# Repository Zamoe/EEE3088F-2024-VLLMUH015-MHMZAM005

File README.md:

# EEE3088F-2024-VLLMUH015-MHMZAM005 - Group 29
Git Repo for EEE3088F group 29 2024 at the University of Cape Town.

The project for EEE3088F aims to design subassemblies for a micromouse, namely the power and sensing subsystem. 
The GitHub repo contains the Kicad Project files for the final PCBs for the project.

The power system is done by Muhammed Vally - VLLMUH015
The sensing subsystem is done by Zameer Mahomed - MHMZAM005

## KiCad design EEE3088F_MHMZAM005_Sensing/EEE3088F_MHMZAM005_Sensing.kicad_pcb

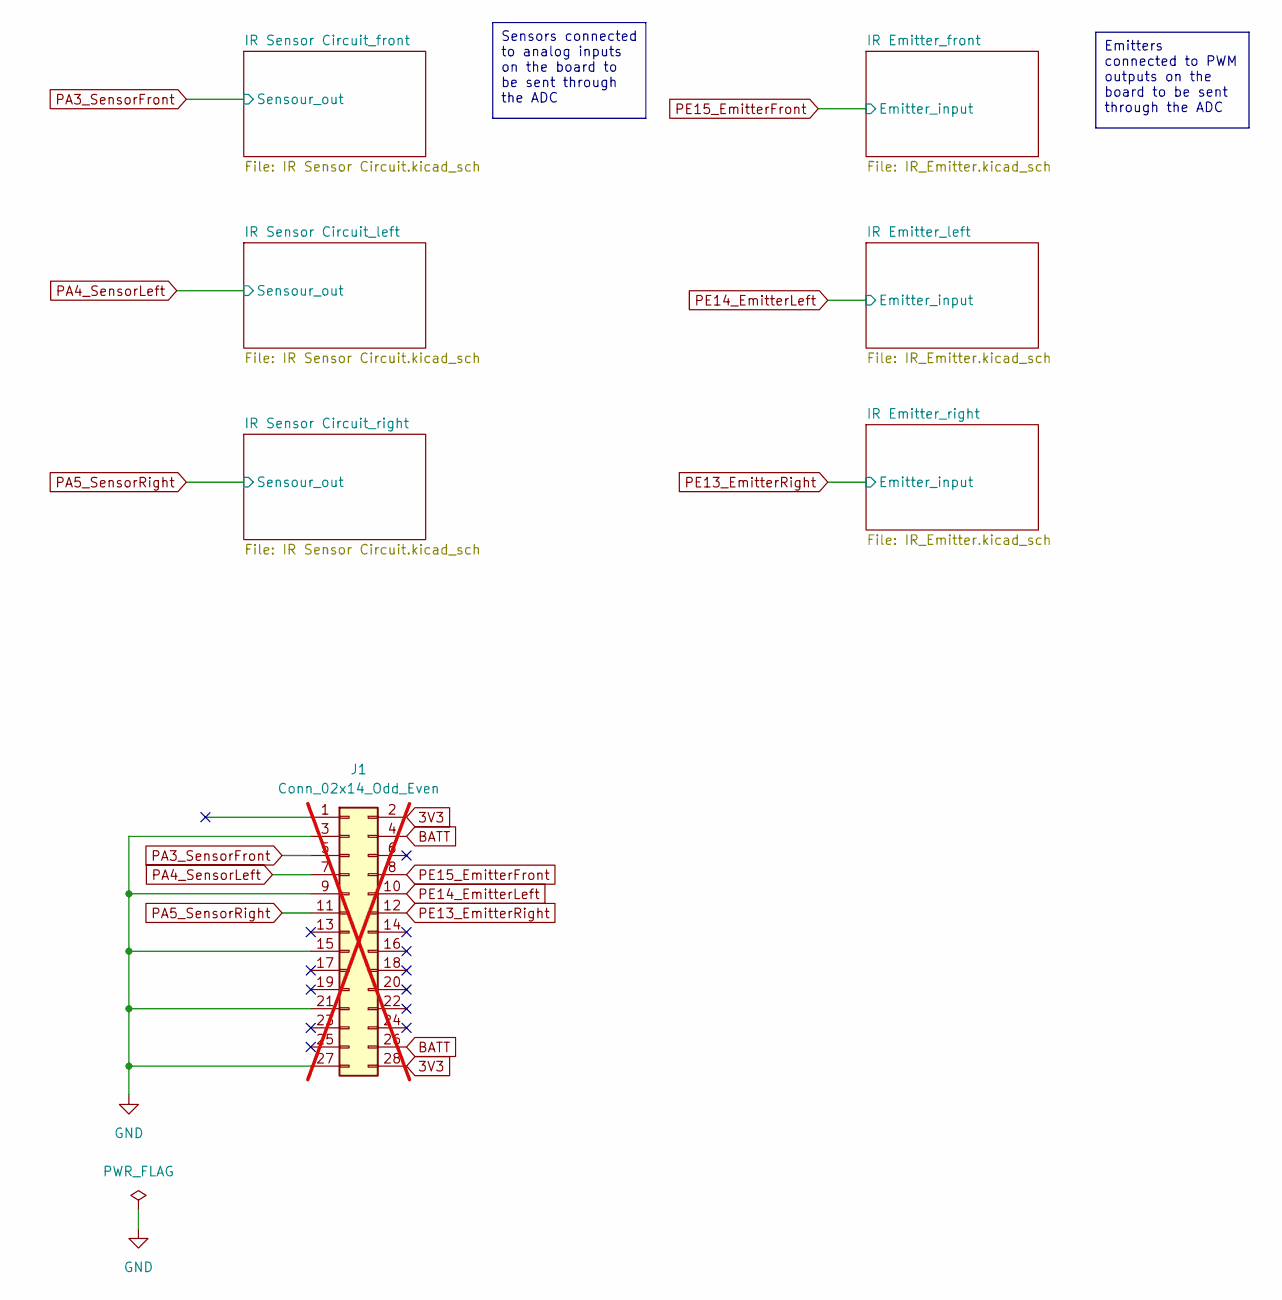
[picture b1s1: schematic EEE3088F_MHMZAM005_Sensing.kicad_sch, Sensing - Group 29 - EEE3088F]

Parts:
J1: Conn_02x14_Odd_Even; PinHeader_2x14_P2.54mm_Vertical; not fitted

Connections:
3V3: J1.2, J1.28; also elsewhere on the board
BATT: J1.4, J1.26
GND: J1.3, J1.9, J1.15, J1.21, J1.27; also elsewhere on the board
PA3: J1.5; also elsewhere on the board
PA4: J1.7; also elsewhere on the board
PA5: J1.11; also elsewhere on the board
PE13: J1.12; also elsewhere on the board
PE14: J1.10; also elsewhere on the board
PE15: J1.8; also elsewhere on the board

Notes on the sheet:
Sensors connected to analog inputs on the board to be sent through the ADC
Emitters connected to PWM outputs on the board to be sent through the ADC

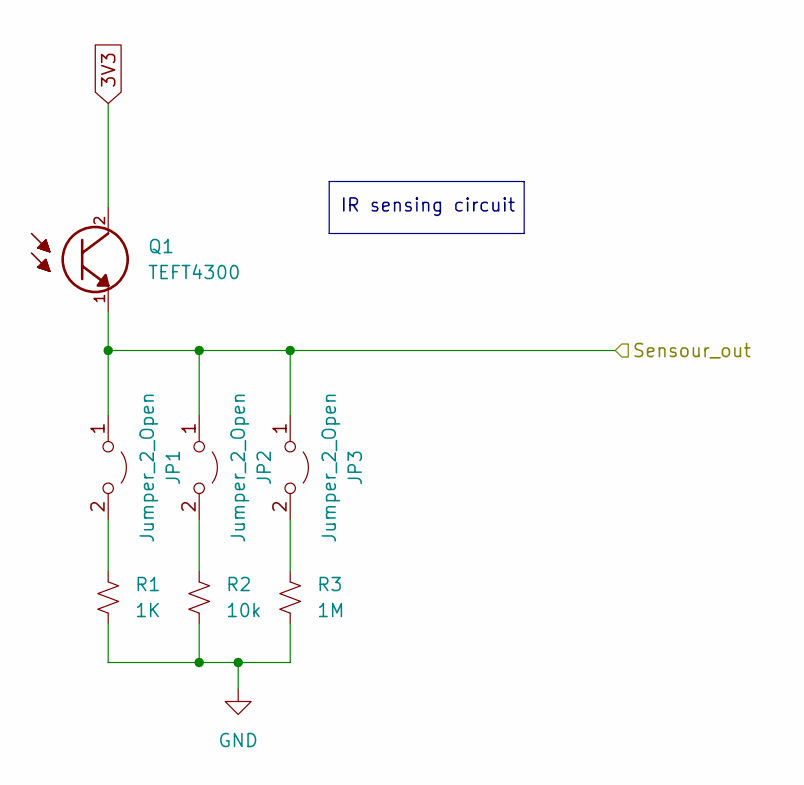
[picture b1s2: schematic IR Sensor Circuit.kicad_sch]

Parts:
JP1, JP2, JP3: Jumper_2_Open; SolderJumper-2_P1.3mm_Open_Pad1.0x1.5mm
Q1: TEFT4300; LED_D3.0mm_Horizontal_O1.27mm_Z2.0mm; LCSC C118301
R1: 1K; R_Axial_DIN0207_L6.3mm_D2.5mm_P2.54mm_Vertical; LCSC C274526
R2: 10k; R_Axial_DIN0207_L6.3mm_D2.5mm_P2.54mm_Vertical; LCSC C274420
R3: 1M; R_Axial_DIN0207_L6.3mm_D2.5mm_P2.54mm_Vertical; LCSC C2894664

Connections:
3V3: Q1.2; also elsewhere on the board
GND: R1.2, R2.2, R3.1; also elsewhere on the board
unnamed: JP1.2 (B), R1.1
unnamed: JP2.2 (B), R2.1
unnamed: JP3.2 (B), R3.2
PA3: JP1.1 (A), JP2.1 (A), JP3.1 (A), Q1.1; also elsewhere on the board

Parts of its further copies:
JP4, JP5, JP6, JP7, JP8, JP9: Jumper_2_Open; SolderJumper-2_P1.3mm_Open_Pad1.0x1.5mm
Q2, Q3: TEFT4300; LED_D3.0mm_Horizontal_O1.27mm_Z2.0mm; LCSC C118301
R4, R7: 1K; R_Axial_DIN0207_L6.3mm_D2.5mm_P2.54mm_Vertical; LCSC C274526
R5, R8: 10k; R_Axial_DIN0207_L6.3mm_D2.5mm_P2.54mm_Vertical; LCSC C274420
R6, R9: 1M; R_Axial_DIN0207_L6.3mm_D2.5mm_P2.54mm_Vertical; LCSC C2894664

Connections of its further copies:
3V3: Q2.2, Q3.2; also elsewhere on the board
GND: R4.2, R5.2, R6.1, R7.2, R8.2, R9.1; also elsewhere on the board
unnamed: JP4.2 (B), R4.1
unnamed: JP5.2 (B), R5.1
unnamed: JP6.2 (B), R6.2
unnamed: JP7.2 (B), R7.1
unnamed: JP8.2 (B), R8.1
unnamed: JP9.2 (B), R9.2
PA4: JP4.1 (A), JP5.1 (A), JP6.1 (A), Q2.1; also elsewhere on the board
PA5: JP7.1 (A), JP8.1 (A), JP9.1 (A), Q3.1; also elsewhere on the board

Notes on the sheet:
IR sensing circuit

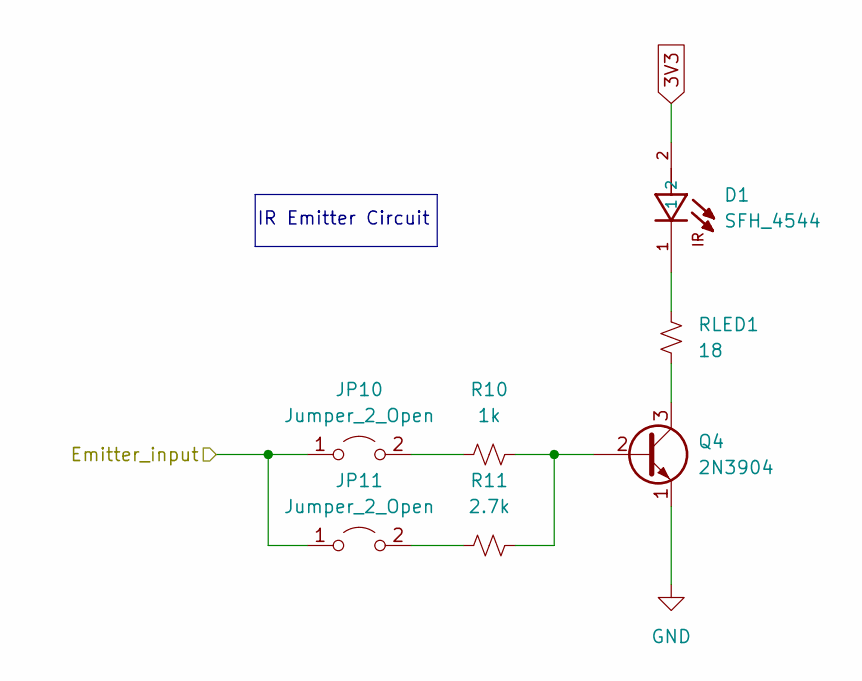
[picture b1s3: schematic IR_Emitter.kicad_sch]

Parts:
D1: SFH_4544; LED_D5.0mm_Horizontal_O1.27mm_Z9.0mm; PARTREV 1.3; LCSC C2900370
JP10, JP11: Jumper_2_Open; SolderJumper-2_P1.3mm_Open_Pad1.0x1.5mm
Q4: 2N3904; TO-92_Inline; LCSC C118538
R10: 1k; R_Axial_DIN0207_L6.3mm_D2.5mm_P2.54mm_Vertical; LCSC C274526
R11: 2.7k; R_Axial_DIN0207_L6.3mm_D2.5mm_P2.54mm_Vertical; LCSC C119880
RLED1: 18; R_Axial_DIN0207_L6.3mm_D2.5mm_P2.54mm_Vertical; LCSC C172523

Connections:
3V3: D1.2; also elsewhere on the board
GND: Q4.1 (E); also elsewhere on the board
unnamed: D1.1, RLED1.2
unnamed: JP10.2 (B), R10.2
unnamed: JP11.2 (B), R11.1
unnamed: Q4.2 (B), R10.1, R11.2
unnamed: Q4.3 (C), RLED1.1
PE15: JP10.1 (A), JP11.1 (A); also elsewhere on the board

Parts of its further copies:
D2, D3: SFH_4544; LED_D5.0mm_Horizontal_O1.27mm_Z9.0mm; PARTREV 1.3; LCSC C2900370
JP12, JP13, JP14, JP15: Jumper_2_Open; SolderJumper-2_P1.3mm_Open_Pad1.0x1.5mm
Q5, Q6: 2N3904; TO-92_Inline; LCSC C118538
R12, R14: 1k; R_Axial_DIN0207_L6.3mm_D2.5mm_P2.54mm_Vertical; LCSC C274526
R13, R15: 2.7k; R_Axial_DIN0207_L6.3mm_D2.5mm_P2.54mm_Vertical; LCSC C119880
RLED2, RLED3: 18; R_Axial_DIN0207_L6.3mm_D2.5mm_P2.54mm_Vertical; LCSC C172523

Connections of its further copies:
3V3: D2.2, D3.2; also elsewhere on the board
GND: Q5.1 (E), Q6.1 (E); also elsewhere on the board
unnamed: D2.1, RLED2.2
unnamed: D3.1, RLED3.2
unnamed: JP12.2 (B), R12.2
unnamed: JP13.2 (B), R13.1
unnamed: JP14.2 (B), R14.2
unnamed: JP15.2 (B), R15.1
unnamed: Q5.2 (B), R12.1, R13.2
unnamed: Q5.3 (C), RLED2.1
unnamed: Q6.2 (B), R14.1, R15.2
unnamed: Q6.3 (C), RLED3.1
PE13: JP14.1 (A), JP15.1 (A); also elsewhere on the board
PE14: JP12.1 (A), JP13.1 (A); also elsewhere on the board

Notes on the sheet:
IR Emitter Circuit

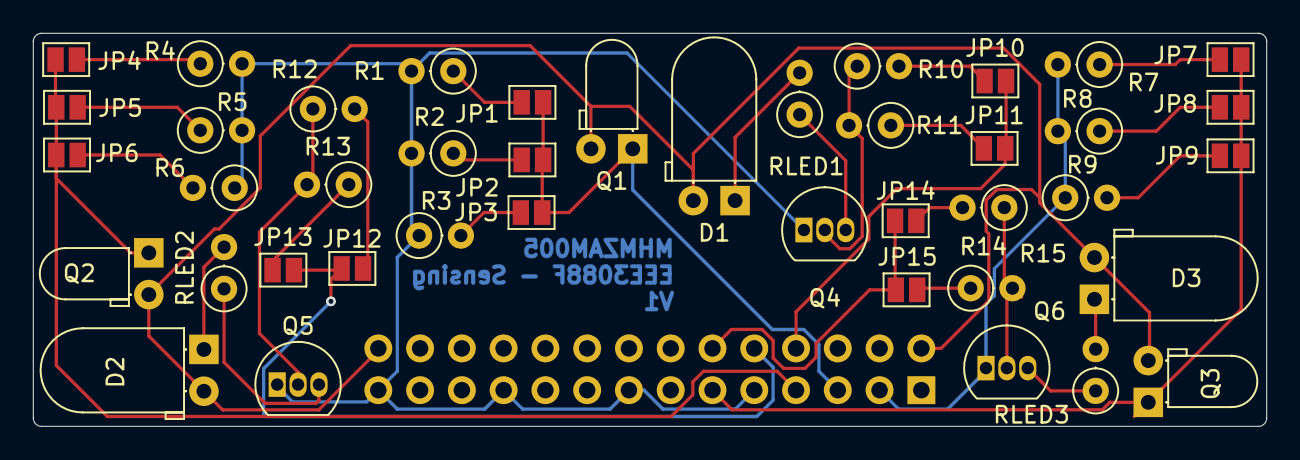
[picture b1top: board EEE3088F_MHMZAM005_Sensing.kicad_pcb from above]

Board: 2 copper layers, 75.0 x 23.9 mm, 43 parts (1 on the bottom side), 33 nets.

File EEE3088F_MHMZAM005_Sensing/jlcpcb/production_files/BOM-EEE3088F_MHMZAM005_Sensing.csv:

Comment,Designator,Footprint,LCSC
TEFT4300,"Q1,Q2,Q3",LED_D3.0mm_Horizontal_O1.27mm_Z2.0mm,C118301
2N3904,"Q4,Q5,Q6",TO-92_Inline,C118538
2.7k,"R11,R13,R15",R_Axial_DIN0207_L6.3mm_D2.5mm_P2.54mm_Vertical,C119880
18,"RLED1,RLED2,RLED3",R_Axial_DIN0207_L6.3mm_D2.5mm_P2.54mm_Vertical,C172523
10k,"R2,R5,R8",R_Axial_DIN0207_L6.3mm_D2.5mm_P2.54mm_Vertical,C274420
1K,"R1,R10,R12,R14,R4,R7",R_Axial_DIN0207_L6.3mm_D2.5mm_P2.54mm_Vertical,C274526
1M,"R3,R6,R9",R_Axial_DIN0207_L6.3mm_D2.5mm_P2.54mm_Vertical,C2894664
SFH_4544,"D1,D2,D3",LED_D5.0mm_Horizontal_O1.27mm_Z9.0mm,C2900370
Jumper_2_Open,JP4,SolderJumper-2_P1.3mm_Open_Pad1.0x1.5mm,
Jumper_2_Open,JP1,SolderJumper-2_P1.3mm_Open_Pad1.0x1.5mm,
Jumper_2_Open,JP15,SolderJumper-2_P1.3mm_Open_Pad1.0x1.5mm,
Jumper_2_Open,JP13,SolderJumper-2_P1.3mm_Open_Pad1.0x1.5mm,
Jumper_2_Open,JP2,SolderJumper-2_P1.3mm_Open_Pad1.0x1.5mm,
Jumper_2_Open,JP7,SolderJumper-2_P1.3mm_Open_Pad1.0x1.5mm,
Jumper_2_Open,JP5,SolderJumper-2_P1.3mm_Open_Pad1.0x1.5mm,
Jumper_2_Open,JP11,SolderJumper-2_P1.3mm_Open_Pad1.0x1.5mm,
Jumper_2_Open,JP9,SolderJumper-2_P1.3mm_Open_Pad1.0x1.5mm,
Jumper_2_Open,JP6,SolderJumper-2_P1.3mm_Open_Pad1.0x1.5mm,
Jumper_2_Open,JP10,SolderJumper-2_P1.3mm_Open_Pad1.0x1.5mm,
Jumper_2_Open,JP14,SolderJumper-2_P1.3mm_Open_Pad1.0x1.5mm,
Jumper_2_Open,JP3,SolderJumper-2_P1.3mm_Open_Pad1.0x1.5mm,
Jumper_2_Open,JP12,SolderJumper-2_P1.3mm_Open_Pad1.0x1.5mm,
Jumper_2_Open,JP8,SolderJumper-2_P1.3mm_Open_Pad1.0x1.5mm,
Conn_02x14_Odd_Even,J1,PinHeader_2x14_P2.54mm_Vertical,

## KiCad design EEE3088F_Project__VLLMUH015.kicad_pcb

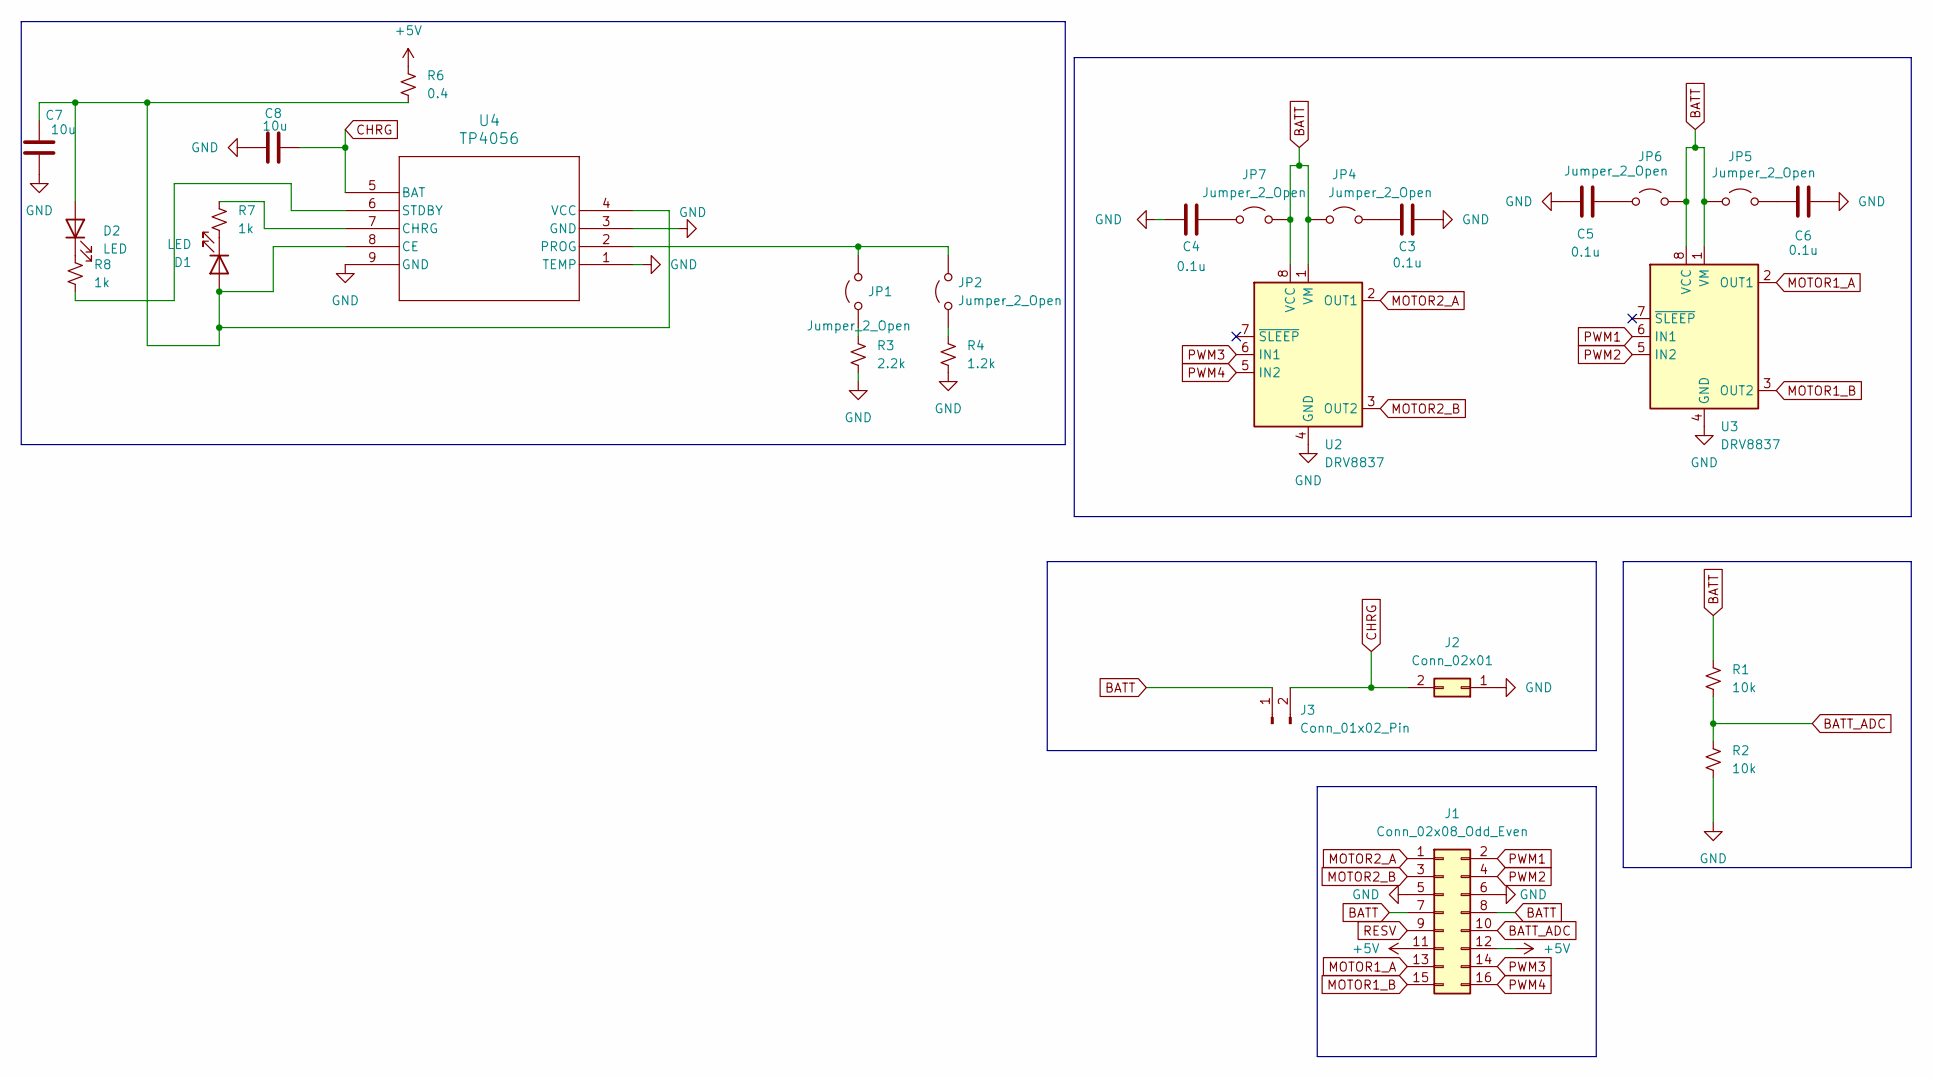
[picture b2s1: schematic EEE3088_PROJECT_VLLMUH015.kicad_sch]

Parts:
C3, C4, C5, C6: 0.1u; C_0805_2012Metric
C7, C8: 10u; C_0805_2012Metric
D1, D2: LED; LED_D1.8mm_W1.8mm_H2.4mm_Horizontal_O1.27mm_Z1.6mm
J1: Conn_02x08_Odd_Even; PinSocket_2x08_P2.54mm_Horizontal
J2: Conn_02x01; PinSocket_1x02_P2.54mm_Vertical
J3: Conn_01x02_Pin; PinHeader_1x02_P2.54mm_Vertical
JP1, JP2, JP4, JP5, JP6, JP7: Jumper_2_Open; SolderJumper-2_P1.3mm_Bridged2Bar_Pad1.0x1.5mm
R1, R2: 10k; R_0805_2012Metric
R3: 2.2k; R_0805_2012Metric
R4: 1.2k; R_0805_2012Metric
R6: 0.4; R_0805_2012Metric
R7, R8: 1k; R_0805_2012Metric
U2, U3: DRV8837; WSON-8-1EP_2x2mm_P0.5mm_EP0.9x1.6mm
U4: TP4056; ESOP8_UMW-L

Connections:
+5V: J1.11, J1.12, R6.1
BATT: J1.7, J1.8, J3.1, JP4.1 (A), JP5.1 (A), JP6.2 (B), JP7.2 (B), R1.1, U2.1 (VM), U2.8 (VCC), U3.1 (VM), U3.8 (VCC)
BATT_ADC: J1.10, R1.2, R2.1
CHRG: C8.2, J2.2, J3.2, U4.5 (BAT)
GND: C3.2, C4.1, C5.1, C6.2, C7.2, C8.1, J1.5, J1.6, J2.1, R2.2, R3.2, R4.2, U2.4 (GND), U2.9 (GND), U3.4 (GND), U3.9 (GND), U4.1 (TEMP), U4.3 (GND), U4.9 (GND)
MOTOR1_A: J1.13, U3.2 (OUT1)
MOTOR1_B: J1.15, U3.3 (OUT2)
MOTOR2_A: J1.1, U2.2 (OUT1)
MOTOR2_B: J1.3, U2.3 (OUT2)
unnamed: C7.1, D1.2 (A), D2.2 (A), R6.2, U4.4 (VCC), U4.8 (CE)
unnamed: D1.1 (K), R7.2
unnamed: D2.1 (K), R8.2
unnamed: JP1.1 (A), R3.1
unnamed: JP1.2 (B), JP2.2 (B), U4.2 (PROG)
unnamed: JP2.1 (A), R4.1
unnamed: C3.1, JP4.2 (B)
unnamed: C6.1, JP5.2 (B)
unnamed: C5.2, JP6.1 (A)
unnamed: C4.2, JP7.1 (A)
unnamed: R7.1, U4.7 (CHRG)
unnamed: R8.1, U4.6 (STDBY)
PWM1: J1.2, U3.6 (IN1)
PWM2: J1.4, U3.5 (IN2)
PWM3: J1.14, U2.6 (IN1)
PWM4: J1.16, U2.5 (IN2)
RESV: J1.9

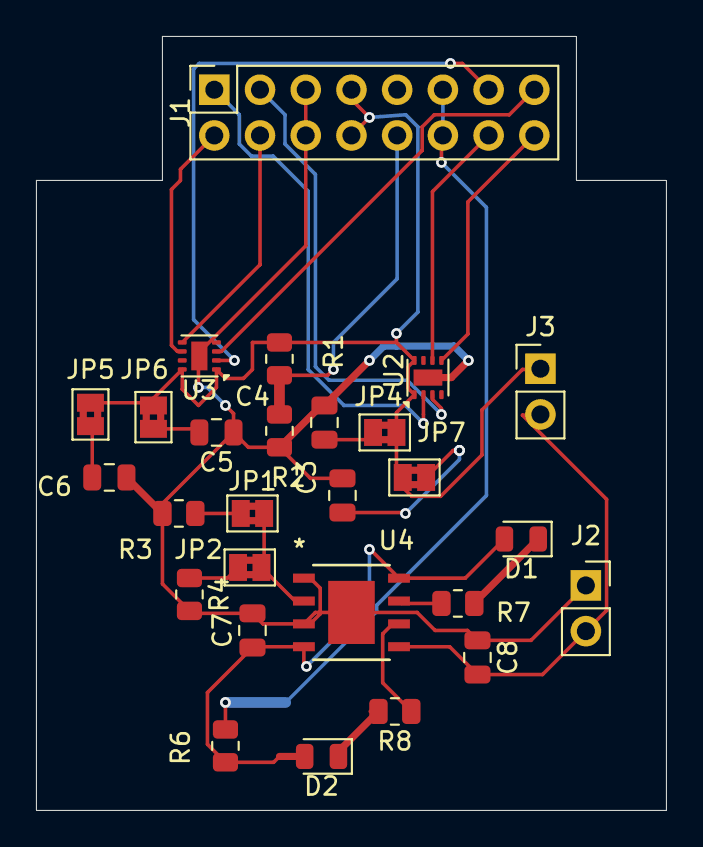
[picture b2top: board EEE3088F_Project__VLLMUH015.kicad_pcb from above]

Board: 2 copper layers, 35.0 x 43.0 mm, 27 parts (0 on the bottom side), 25 nets.

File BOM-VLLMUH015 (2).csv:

Comment,Designator,Footprint,LCSC
0.1u,C6,C_0805_2012Metric,
10k,R2,R_0805_2012Metric,
0.1u,C5,C_0805_2012Metric,
0.1u,C3,C_0805_2012Metric,
Jumper_2_Open,JP5,SolderJumper-2_P1.3mm_Bridged2Bar_Pad1.0x1.5mm,
1.1k,R4,R_0805_2012Metric,
Jumper_2_Open,JP4,SolderJumper-2_P1.3mm_Bridged2Bar_Pad1.0x1.5mm,
2.2k,R3,R_0805_2012Metric,
10k,R1,R_0805_2012Metric,
Conn_02x01,J2,PinSocket_1x02_P2.54mm_Vertical,
Jumper_2_Open,JP7,SolderJumper-2_P1.3mm_Bridged2Bar_Pad1.0x1.5mm,
Jumper_2_Open,JP2,SolderJumper-2_P1.3mm_Bridged2Bar_Pad1.0x1.5mm,
Jumper_2_Open,JP1,SolderJumper-2_P1.3mm_Bridged2Bar_Pad1.0x1.5mm,
0.1u,C4,C_0805_2012Metric,
Conn_02x08_Odd_Even,J1,PinSocket_2x08_P2.54mm_Vertical,
DRV8837,U2,WSON-8-1EP_2x2mm_P0.5mm_EP0.9x1.6mm,
LED,D1,LED_0805_2012Metric,
Jumper_2_Open,JP6,SolderJumper-2_P1.3mm_Bridged2Bar_Pad1.0x1.5mm,
DRV8837,U3,WSON-8-1EP_2x2mm_P0.5mm_EP0.9x1.6mm,
LED,D2,LED_0805_2012Metric,
10u,C8,C_0805_2012Metric,
0.4,R6,R_0805_2012Metric,
Conn_01x02_Pin,J3,PinHeader_1x02_P2.54mm_Vertical,
TP4056,U4,ESOP8_UMW-L,
10u,C7,C_0805_2012Metric,
1k,R7,R_0805_2012Metric,
1k,R8,R_0805_2012Metric,

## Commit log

2024-05-17 Code to interface UCT STM32 board with Sensing subsystem
